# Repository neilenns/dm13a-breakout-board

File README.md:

# DM13A breakout board

Breakout board for the DM13A LED driver, for use with MobiFlight. This is completely untested and not intended for real-world use. The goal of this repo was to explore using KiCad 9 command line tools to automate releases of the design, including schematics, board images, and JLCPCB fabrication files.

## Highlights

Highlights

- A VSCode devcontainer is included that includes the `kicad-cli` command for local development.
- A `tasks.json` file is included to enable quick local testing of the jobset generation.
- Outputs are defined using KiCad [jobsets](https://docs.kicad.org/9.0/en/kicad/kicad.html#jobsets).
- Variables are used to specify a version and date stamp. These are used in the sheet data blocks as well as the silkscreen on the board.
- A GitHub [workflow](https://github.com/neilenns/dm13a-breakout-board/blob/main/.github/workflows/release.yaml) runs when a GitHub release is created, or when triggered manually, to produce all the output files. The version variable is set to the GitHub release version and the date stamp is set to the year, month, and day of the GitHub release.
- Output files are modified by the workflow to match the JLCPCB upload requirements.
- The completed outputs are uploaded to the [release](https://github.com/neilenns/dm13a-breakout-board/releases) for easy access.
- Board images are automatically checked in to the docs directory via an auto-merged pull request, for use in this readme.

## Generated outputs

- [Schematic](https://github.com/neilenns/dm13a-breakout-board/releases/latest/download/dm13a-breakout-board-schematic.pdf)
- [Documentation zip](https://github.com/neilenns/dm13a-breakout-board/releases/latest/download/dm13a-breakout-board-documentation.zip), including schematic and PCB images
- [JLCPCB submission zip](https://github.com/neilenns/dm13a-breakout-board/releases/latest/download/dm13a-breakout-board-JLCPCB.zip), including gerbers, drill position, BOM, and CPL files

## Using this in your own project

For everything to work correctly the GitHub repository name must exactly match the KiCad project name. For example, this repo is named `dm13a-breakout-board` and the project is `dm13a-breakout-board.kicad_pro`.

> [!IMPORTANT]
> The workflow and jobset depend on the GitHub repository and KiCad project name being exactly the same. If they don't match,
> none of this will work.

Copy the following two files into the same location in your repository:

- `.github/workflows/release.yaml`: The GitHub workflow for releases.
- `jobs.kicad_jobset`: The jobset that defines the outputs required for the release.

In your project, use the `VERSION` variable wherever the version number should get placed, and the `DATE` variable wherever the date should be placed.

To make a new release simply use the GitHub release feature. The resulting files will get attached to the release, and the updated board images will be merged into the `docs/` folder of the repo.

Don't forget that KiCad has [integrated git commands](https://docs.kicad.org/9.0/en/kicad/kicad.html#git_integration) for committing and pushing changes!

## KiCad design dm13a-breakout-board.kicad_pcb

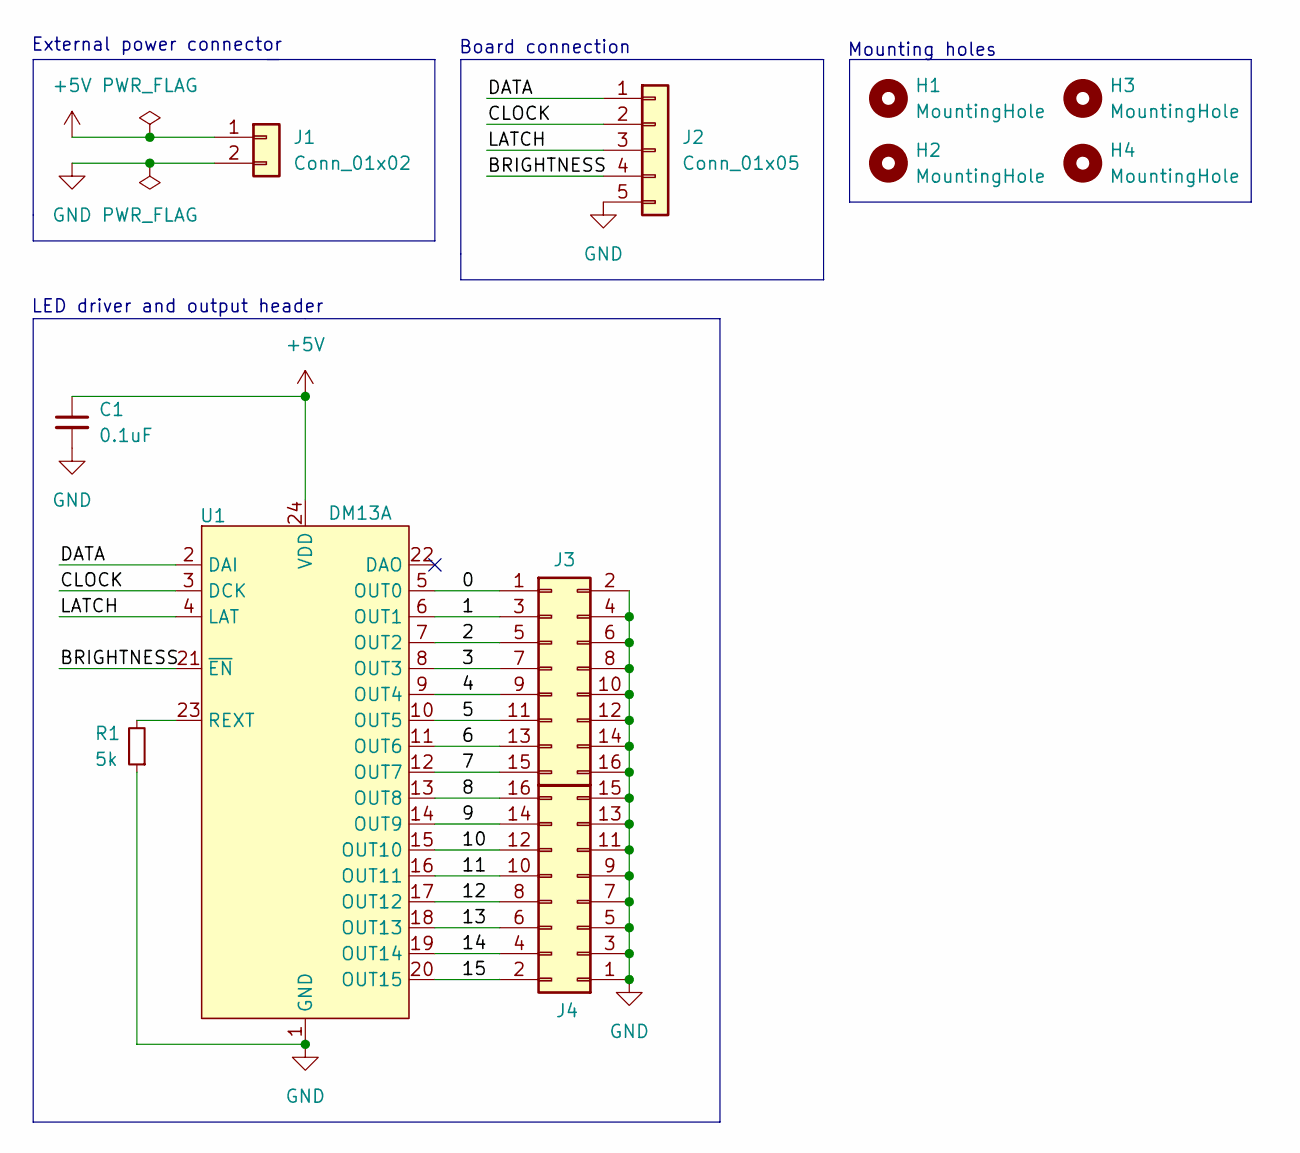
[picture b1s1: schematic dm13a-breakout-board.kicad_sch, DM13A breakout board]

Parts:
C1: 0.1uF; C_0603_1608Metric; LCSC package 0603
H1, H2, H3, H4: MountingHole; MountingHole_3.2mm_M3
J1: Conn_01x02; PinHeader_1x02_P2.54mm_Vertical
J2: Conn_01x05; PinHeader_1x05_P2.54mm_Vertical
J3, J4: Conn_02x08_Odd_Even; PinSocket_2x08_P2.54mm_Vertical
R1: 5k; R_Axial_DIN0411_L9.9mm_D3.6mm_P12.70mm_Horizontal
U1: DM13A; DIP-24_W7.62mm

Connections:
+5V: C1.1, J1.1, U1.24 (VDD)
/0: J3.1, U1.5 (OUT0)
/1: J3.3, U1.6 (OUT1)
/2: J3.5, U1.7 (OUT2)
/3: J3.7, U1.8 (OUT3)
/4: J3.9, U1.9 (OUT4)
/5: J3.11, U1.10 (OUT5)
/6: J3.13, U1.11 (OUT6)
/7: J3.15, U1.12 (OUT7)
/8: J4.16, U1.13 (OUT8)
/9: J4.14, U1.14 (OUT9)
/10: J4.12, U1.15 (OUT10)
/11: J4.10, U1.16 (OUT11)
/12: J4.8, U1.17 (OUT12)
/13: J4.6, U1.18 (OUT13)
/14: J4.4, U1.19 (OUT14)
/15: J4.2, U1.20 (OUT15)
/BRIGHTNESS: J2.4, U1.21 (~EN)
/CLOCK: J2.2, U1.3 (DCK)
/DATA: J2.1, U1.2 (DAI)
/LATCH: J2.3, U1.4 (LAT)
GND: C1.2, J1.2, J2.5, J3.2, J3.4, J3.6, J3.8, J3.10, J3.12, J3.14, J3.16, J4.1, J4.3, J4.5, J4.7, J4.9, J4.11, J4.13, J4.15, R1.1, U1.1 (GND)
unnamed: R1.2, U1.23 (REXT)

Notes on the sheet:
LED driver and output header
Board connection
Mounting holes
External power connector

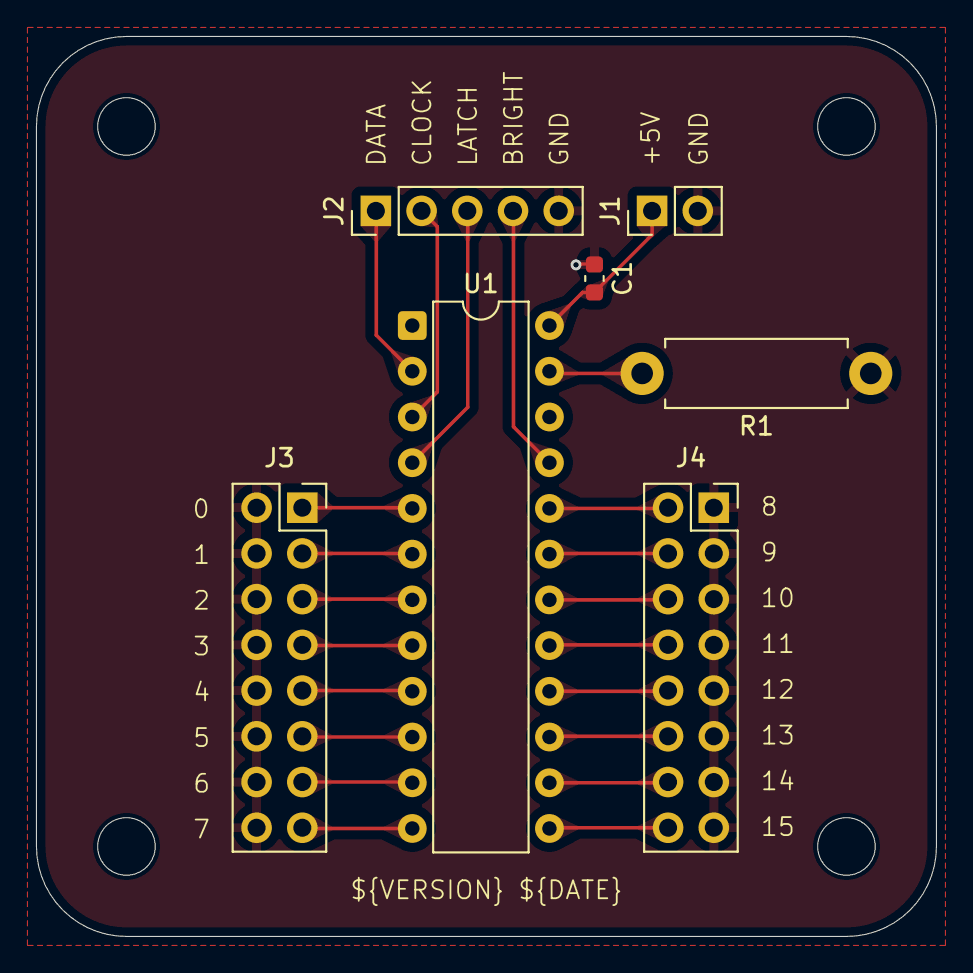
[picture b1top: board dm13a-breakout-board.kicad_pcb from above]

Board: 2 copper layers, 50.0 x 50.0 mm, 11 parts (0 on the bottom side), 23 nets.

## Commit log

2025-02-24 Add basic devcontainer
2025-02-24 Super basic schematic for testing purposes
2025-02-24 Attempt the initial version
2025-02-24 Try fixing the runner
2025-02-24 Try again
2025-02-24 Attach the artifact
2025-02-24 update version
2025-02-24 Don't fail on errors
2025-02-24 Trying yet again
2025-02-24 What
2025-02-24 Quotes maybe?
2025-02-24 Try copying files
2025-02-24 Use bash
2025-02-24 Try sudo
2025-02-24 Try direct install
2025-02-24 sudo
2025-02-24 Try copying the libraries over
2025-02-24 Try the runner folder
2025-02-24 Try with caching action
2025-02-24 Fix path
2025-02-24 Try adding via the action
2025-02-24 force rebuild
2025-02-24 Fix cache hit test
2025-02-24 Add library caching
2025-02-24 Move where version check happens
2025-02-24 Try changing to timestamp
2025-02-24 Remove unneeded or
2025-02-24 Use Docker image instead
2025-02-24 Configure BOM stuff
2025-02-24 Try generating stuff
2025-02-24 Fix version
2025-02-24 Get rid of variables from BOM
2025-02-24 Fix artifact path
2025-02-24 Use project name instead
2025-02-24 Add release action
2025-02-24 Update action version
2025-02-24 More tweaks to zipping
2025-02-24 More release fixes
2025-02-25 Try yet again
2025-02-25 Update working directory
2025-02-25 Try the whole thing
2025-02-25 Fix the yaml
2025-02-25 Make bash the default shell
2025-02-25 Sheesh
2025-02-25 Try fixing manual version
2025-02-25 Fix again
2025-02-25 Add artifact upload
2025-02-25 Lol chatgpt fail
2025-02-25 ChatGPT is so dumb
2025-02-25 Add renovate.json
2025-02-25 Update actions/checkout action to v4
2025-02-25 Try changing to jobsets
2025-02-25 More job generation
2025-02-25 Fix filenames
2025-02-25 Fix some file extensions
2025-02-25 Zip gerbers for JLCPCB Fixes #7
2025-02-25 Fix filenames, comments
2025-02-25 Try fixing zip paths
2025-02-25 Fix filename and delete folder
2025-02-25 Fix missing &&
2025-02-25 Fix BOM generation
2025-02-25 Fix JLCPCB stuff (#9)
    * Zip gerbers for JLCPCB
    Fixes #7
    * Fix filenames, comments
    * Try fixing zip paths
    * Fix filename and delete folder
    * Fix missing &&
2025-02-26 Add generating images
2025-02-26 Set safe directory
2025-02-26 Try PR method instead
2025-02-26 Update branch name
2025-02-26 Try setting base
2025-02-26 Grant pull request permission
2025-02-26 [create-pull-request] automated change
2025-02-26 Set the token
2025-02-26 Try a different token?
2025-02-26 Finally?
2025-02-26 Trust the workspace omg
2025-02-26 Squash instead of merge
2025-02-26 [create-pull-request] automated change (#16)
2025-02-27 Add hash to the version
2025-02-27 Add git command early in process
2025-02-27 [create-pull-request] automated change (#18)
2025-02-27 Center text on PCB
2025-02-27 Exclude image PRs from changelog
2025-02-27 [create-pull-request] automated change (#19)
2025-02-27 Use different connector, add gnd pins, add silkscreen
2025-02-27 [create-pull-request] automated change (#20)
2025-02-27 Simplify JLCPCB gerber generation
2025-02-27 Create output directory recursively
2025-02-27 [create-pull-request] automated change (#21)
2025-02-27 Document how to use it
2025-02-27 Update silkscreen and component placement
2025-02-27 Add note to readme about KiCad git integration
2025-02-27 Silkscreen updates (#22)
    * Update silkscreen and component placement
    * Add note to readme about KiCad git integration
2025-02-27 [create-pull-request] automated change (#23)
2025-08-15 Update actions/checkout action to v5
2025-12-11 Update peter-evans/create-pull-request action to v8
2025-12-11 Update peter-evans/create-pull-request action to v8 (#27)
2025-12-12 Update actions/upload-artifact action to v6
2025-12-12 Update actions/upload-artifact action to v6 (#25)
2025-12-15 Update actions/checkout action to v6
2025-12-16 Update actions/checkout action to v6 (#26)
2026-04-12 Update softprops/action-gh-release action to v3
2026-04-12 Update softprops/action-gh-release action to v3 (#29)
2026-04-15 Update actions/upload-artifact action to v7
2026-04-15 Update actions/upload-artifact action to v7 (#28)

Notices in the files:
dm13a-breakout-board.kicad_pcb:
License: MIT
